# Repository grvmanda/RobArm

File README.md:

# RobArm

potential 6 DOF (maybe lower) 3D printed robotic arm. 

The repo is very rudimentary at the moment (CAD stored on Fusion 360's cloud); the code is based on ROS melodic.
The target platform is RPi4.

Custom stepper motor driver board (and boards for limit switches) designed on KiCad are also stored on this repo.

preview of rev 1 driver board:

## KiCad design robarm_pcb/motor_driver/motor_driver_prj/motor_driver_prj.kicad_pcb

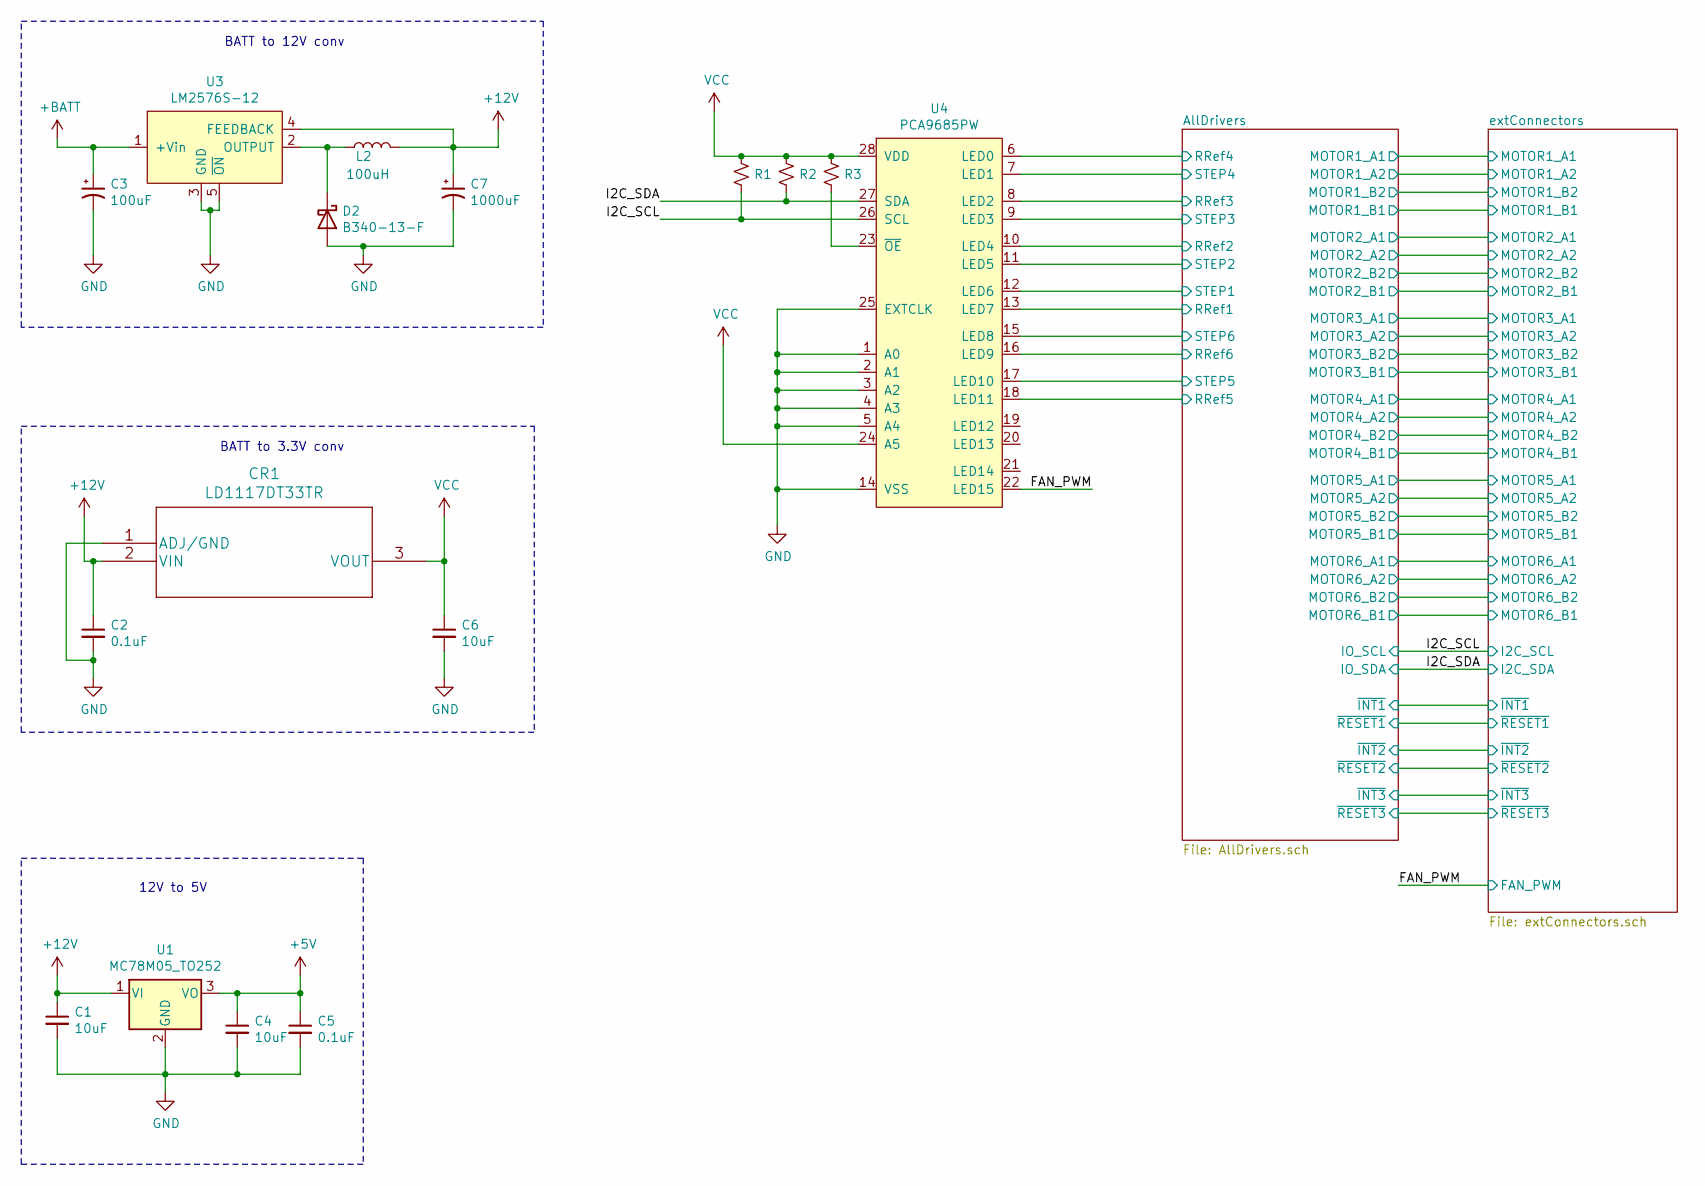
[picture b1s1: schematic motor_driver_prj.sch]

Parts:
C1, C4, C6: 10uF; C_0805_2012Metric_Pad1.18x1.45mm_HandSolder
C2, C5: 0.1uF; C_0603_1608Metric_Pad1.08x0.95mm_HandSolder
C3: 100uF; CP_Elec_8x6.2
C7: 1000uF; CP_Elec_8x6.2
CR1: LD1117DT33TR
D2: B340-13-F
L2: 100uH; SRR1280A-101M
R1, R2, R3: R_Small_US; R_0603_1608Metric_Pad0.98x0.95mm_HandSolder
U1: MC78M05_TO252; TO-252-2
U3: LM2576S-12; LM2576SX_TO263-5
U4: PCA9685PW; PC9685_TSSOP28

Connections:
+5V: C4.1, C5.1, U1.3 (VO); also elsewhere on the board
+12V: C1.1, C2.1, C7.1, CR1.2 (VIN), L2.2, U1.1 (VI), U3.4 (FEEDBACK); also elsewhere on the board
+BATT: C3.1, U3.1 (+Vin); also elsewhere on the board
/AllDrivers/RRef1: U4.13 (LED7); also elsewhere on the board
/AllDrivers/RRef2: U4.10 (LED4); also elsewhere on the board
/AllDrivers/RRef3: U4.8 (LED2); also elsewhere on the board
/AllDrivers/RRef4: U4.6 (LED0); also elsewhere on the board
/AllDrivers/RRef5: U4.18 (LED11); also elsewhere on the board
/AllDrivers/RRef6: U4.16 (LED9); also elsewhere on the board
/AllDrivers/STEP1: U4.12 (LED6); also elsewhere on the board
/AllDrivers/STEP2: U4.11 (LED5); also elsewhere on the board
/AllDrivers/STEP3: U4.9 (LED3); also elsewhere on the board
/AllDrivers/STEP4: U4.7 (LED1); also elsewhere on the board
/AllDrivers/STEP5: U4.17 (LED10); also elsewhere on the board
/AllDrivers/STEP6: U4.15 (LED8); also elsewhere on the board
/FAN_PWM: U4.22 (LED15); also elsewhere on the board
/I2C_SCL: R1.2, U4.26 (SCL); also elsewhere on the board
/I2C_SDA: R2.2, U4.27 (SDA); also elsewhere on the board
GND: C1.2, C2.2, C3.2, C4.2, C5.2, C6.2, C7.2, CR1.1 (ADJ/GND), D2.2 (A), U1.2 (GND), U3.3 (GND), U3.5 (~ON), U4.1 (A0), U4.2 (A1), U4.3 (A2), U4.4 (A3), U4.5 (A4), U4.14 (VSS), U4.25 (EXTCLK); also elsewhere on the board
unnamed: D2.1 (K), L2.1, U3.2 (OUTPUT)
unnamed: R3.2, U4.23 (~OE)
VCC: C6.1, CR1.3 (VOUT), R1.1, R2.1, R3.1, U4.24 (A5), U4.28 (VDD); also elsewhere on the board

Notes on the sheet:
BATT to 12V conv
12V to 5V
BATT to 3.3V conv

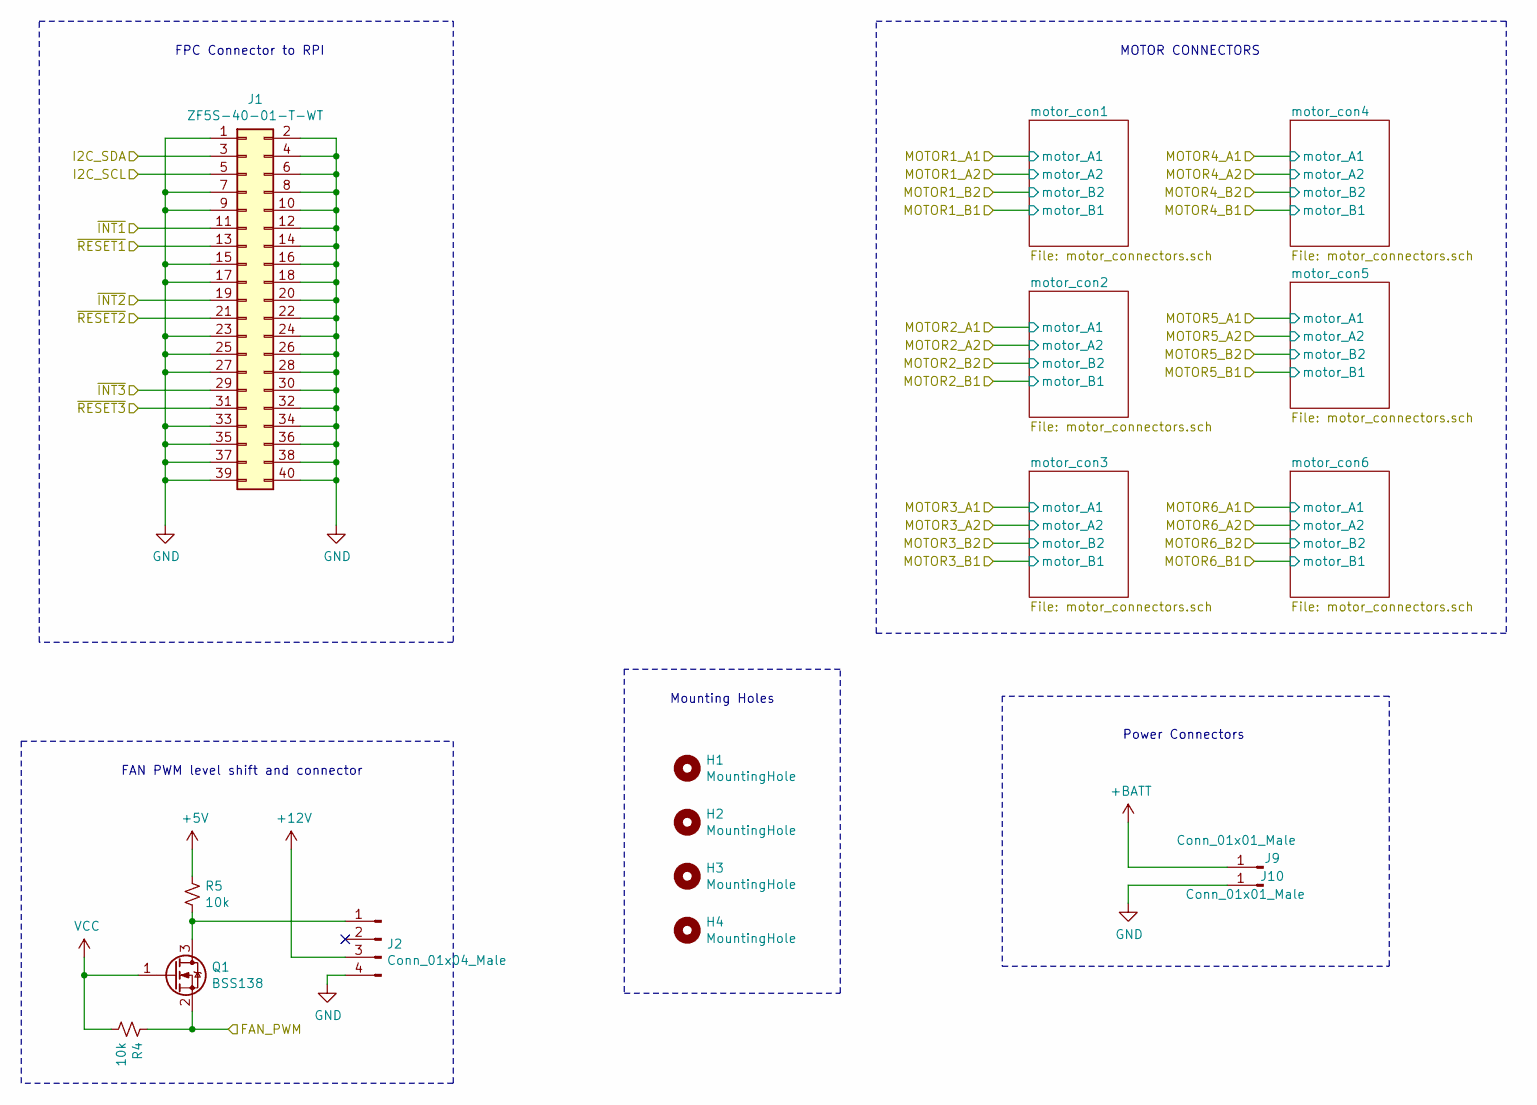
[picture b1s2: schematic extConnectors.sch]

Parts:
H1, H2, H3, H4: MountingHole; MountingHole_3.2mm_M3_ISO14580
J1: ZF5S-40-01-T-WT; FPC_40
J2: Conn_01x04_Male; FanPinHeader_1x04_P2.54mm_Vertical
J9, J10: Conn_01x01_Male; TestPoint_Pad_4.0x4.0mm
Q1: BSS138; SOT-23
R4, R5: 10k; R_0603_1608Metric_Pad0.98x0.95mm_HandSolder

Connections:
+5V: R5.1; also elsewhere on the board
+12V: J2.3; also elsewhere on the board
+BATT: J9.1; also elsewhere on the board
/AllDrivers/~INT1: J1.11; also elsewhere on the board
/AllDrivers/~INT2: J1.19; also elsewhere on the board
/AllDrivers/~INT3: J1.29; also elsewhere on the board
/AllDrivers/~RESET1: J1.13; also elsewhere on the board
/AllDrivers/~RESET2: J1.21; also elsewhere on the board
/AllDrivers/~RESET3: J1.31; also elsewhere on the board
/FAN_PWM: Q1.2 (S), R4.1; also elsewhere on the board
/I2C_SCL: J1.5; also elsewhere on the board
/I2C_SDA: J1.3; also elsewhere on the board
GND: J1.1, J1.2, J1.4, J1.6, J1.7, J1.8, J1.9, J1.10, J1.12, J1.14, J1.15, J1.16, J1.17, J1.18, J1.20, J1.22, J1.23, J1.24, J1.25, J1.26, J1.27, J1.28, J1.30, J1.32, J1.33, J1.34, J1.35, J1.36, J1.37, J1.38, J1.39, J1.40, J2.4, J10.1; also elsewhere on the board
unnamed: J2.1, Q1.3 (D), R5.2
VCC: Q1.1 (G), R4.2; also elsewhere on the board

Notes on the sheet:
MOTOR CONNECTORS
FPC Connector to RPI
FAN PWM level shift and connector
Power Connectors
Mounting Holes

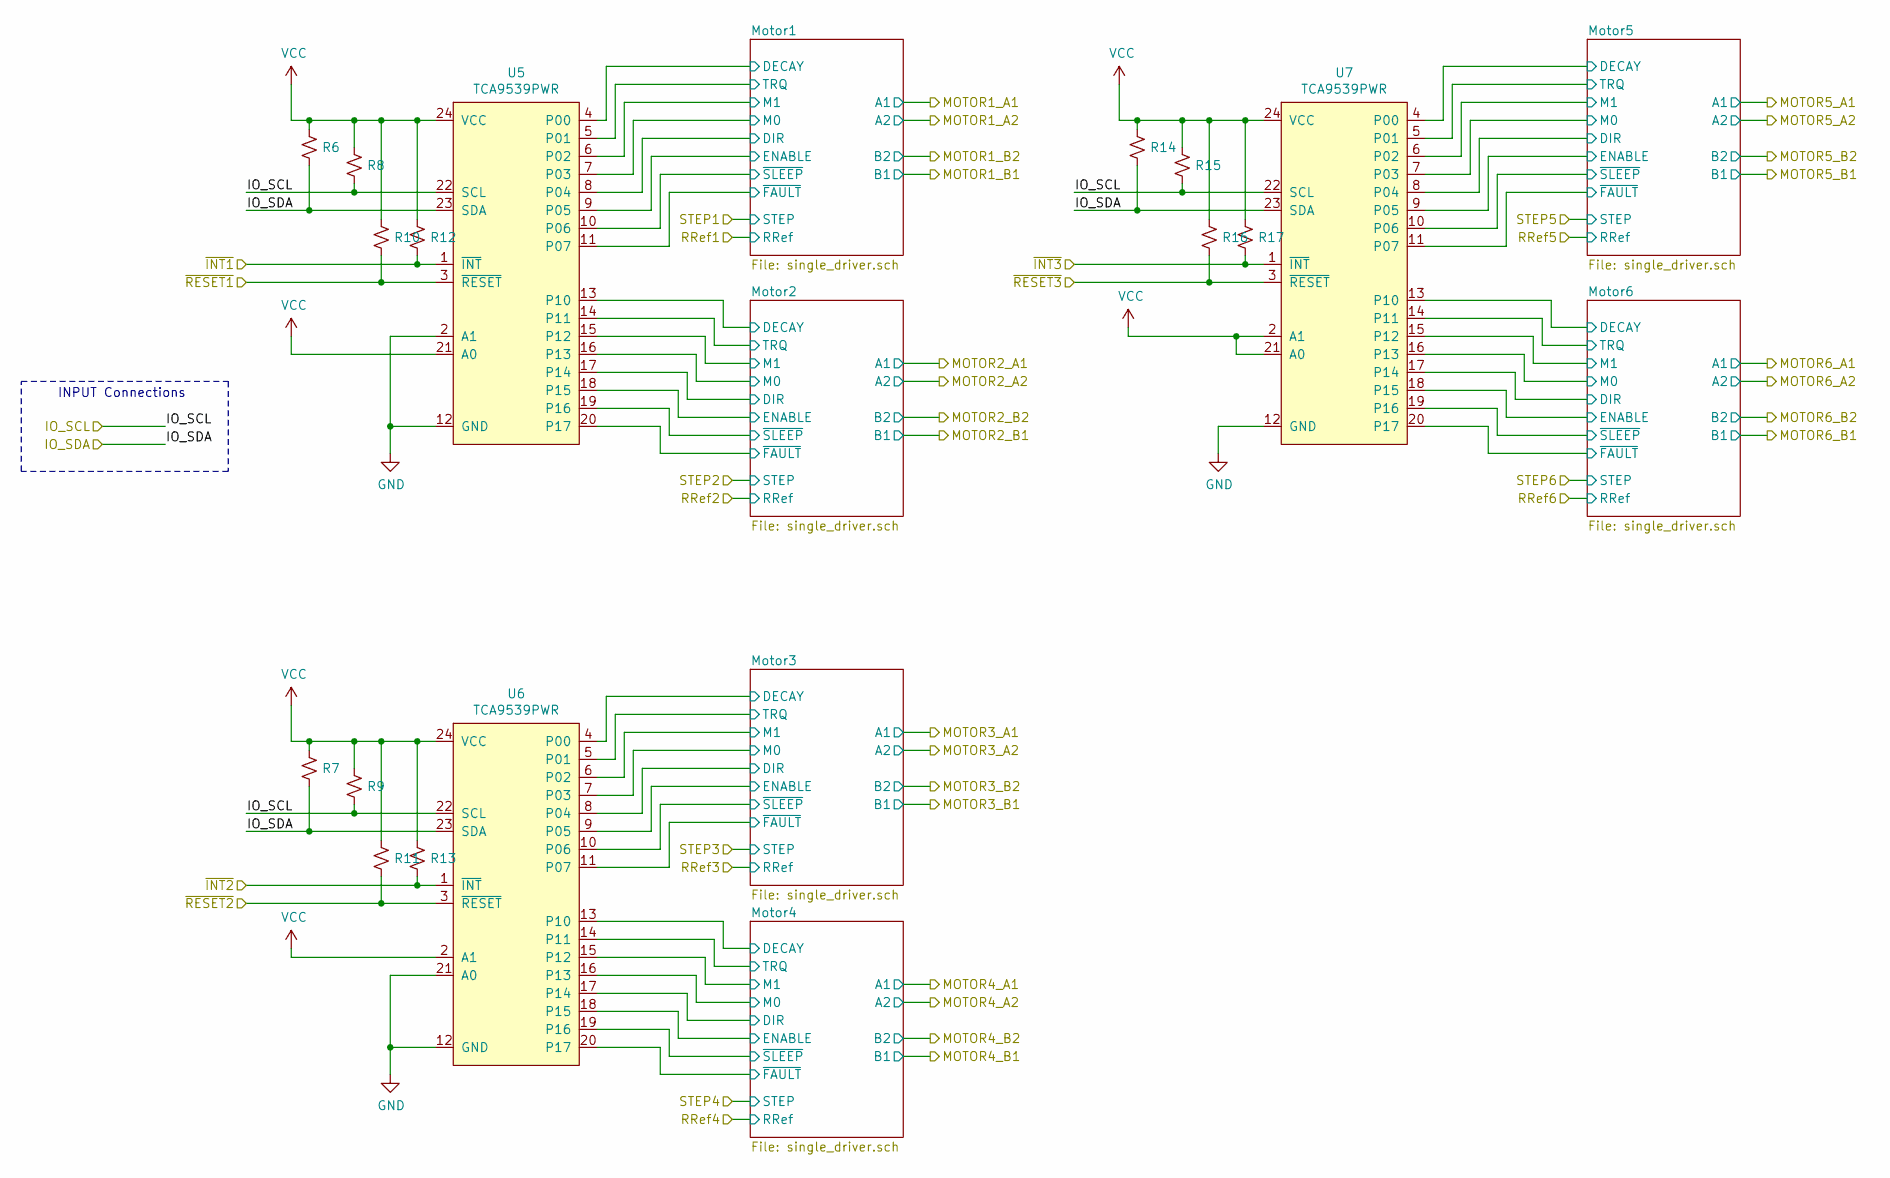
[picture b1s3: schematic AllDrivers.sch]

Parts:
R6, R7, R8, R9, R10, R11, R12, R13, R14, R15, R16, R17: 1; R_0603_1608Metric_Pad0.98x0.95mm_HandSolder
U5, U6, U7: TCA9539PWR; TCA9539_TSSOP-24

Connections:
/AllDrivers/Motor1/DECAY: U5.4 (P00); also elsewhere on the board
/AllDrivers/Motor1/DIR: U5.8 (P04); also elsewhere on the board
/AllDrivers/Motor1/ENABLE: U5.9 (P05); also elsewhere on the board
/AllDrivers/Motor1/M0: U5.7 (P03); also elsewhere on the board
/AllDrivers/Motor1/M1: U5.6 (P02); also elsewhere on the board
/AllDrivers/Motor1/TRQ: U5.5 (P01); also elsewhere on the board
/AllDrivers/Motor1/~FAULT: U5.11 (P07); also elsewhere on the board
/AllDrivers/Motor1/~SLEEP: U5.10 (P06); also elsewhere on the board
/AllDrivers/Motor2/DECAY: U5.13 (P10); also elsewhere on the board
/AllDrivers/Motor2/DIR: U5.17 (P14); also elsewhere on the board
/AllDrivers/Motor2/ENABLE: U5.18 (P15); also elsewhere on the board
/AllDrivers/Motor2/M0: U5.16 (P13); also elsewhere on the board
/AllDrivers/Motor2/M1: U5.15 (P12); also elsewhere on the board
/AllDrivers/Motor2/TRQ: U5.14 (P11); also elsewhere on the board
/AllDrivers/Motor2/~FAULT: U5.20 (P17); also elsewhere on the board
/AllDrivers/Motor2/~SLEEP: U5.19 (P16); also elsewhere on the board
/AllDrivers/Motor3/DECAY: U6.4 (P00); also elsewhere on the board
/AllDrivers/Motor3/DIR: U6.8 (P04); also elsewhere on the board
/AllDrivers/Motor3/ENABLE: U6.9 (P05); also elsewhere on the board
/AllDrivers/Motor3/M0: U6.7 (P03); also elsewhere on the board
/AllDrivers/Motor3/M1: U6.6 (P02); also elsewhere on the board
/AllDrivers/Motor3/TRQ: U6.5 (P01); also elsewhere on the board
/AllDrivers/Motor3/~FAULT: U6.11 (P07); also elsewhere on the board
/AllDrivers/Motor3/~SLEEP: U6.10 (P06); also elsewhere on the board
/AllDrivers/Motor4/DECAY: U6.13 (P10); also elsewhere on the board
/AllDrivers/Motor4/DIR: U6.17 (P14); also elsewhere on the board
/AllDrivers/Motor4/ENABLE: U6.18 (P15); also elsewhere on the board
/AllDrivers/Motor4/M0: U6.16 (P13); also elsewhere on the board
/AllDrivers/Motor4/M1: U6.15 (P12); also elsewhere on the board
/AllDrivers/Motor4/TRQ: U6.14 (P11); also elsewhere on the board
/AllDrivers/Motor4/~FAULT: U6.20 (P17); also elsewhere on the board
/AllDrivers/Motor4/~SLEEP: U6.19 (P16); also elsewhere on the board
/AllDrivers/Motor5/DECAY: U7.4 (P00); also elsewhere on the board
/AllDrivers/Motor5/DIR: U7.8 (P04); also elsewhere on the board
/AllDrivers/Motor5/ENABLE: U7.9 (P05); also elsewhere on the board
/AllDrivers/Motor5/M0: U7.7 (P03); also elsewhere on the board
/AllDrivers/Motor5/M1: U7.6 (P02); also elsewhere on the board
/AllDrivers/Motor5/TRQ: U7.5 (P01); also elsewhere on the board
/AllDrivers/Motor5/~FAULT: U7.11 (P07); also elsewhere on the board
/AllDrivers/Motor5/~SLEEP: U7.10 (P06); also elsewhere on the board
/AllDrivers/Motor6/DECAY: U7.13 (P10); also elsewhere on the board
/AllDrivers/Motor6/DIR: U7.17 (P14); also elsewhere on the board
/AllDrivers/Motor6/ENABLE: U7.18 (P15); also elsewhere on the board
/AllDrivers/Motor6/M0: U7.16 (P13); also elsewhere on the board
/AllDrivers/Motor6/M1: U7.15 (P12); also elsewhere on the board
/AllDrivers/Motor6/TRQ: U7.14 (P11); also elsewhere on the board
/AllDrivers/Motor6/~FAULT: U7.20 (P17); also elsewhere on the board
/AllDrivers/Motor6/~SLEEP: U7.19 (P16); also elsewhere on the board
/AllDrivers/~INT1: R12.2, U5.1 (~INT); also elsewhere on the board
/AllDrivers/~INT2: R13.2, U6.1 (~INT); also elsewhere on the board
/AllDrivers/~INT3: R17.2, U7.1 (~INT); also elsewhere on the board
/AllDrivers/~RESET1: R10.2, U5.3 (~RESET); also elsewhere on the board
/AllDrivers/~RESET2: R11.2, U6.3 (~RESET); also elsewhere on the board
/AllDrivers/~RESET3: R16.2, U7.3 (~RESET); also elsewhere on the board
/I2C_SCL: R8.2, R9.2, R15.2, U5.22 (SCL), U6.22 (SCL), U7.22 (SCL); also elsewhere on the board
/I2C_SDA: R6.2, R7.2, R14.2, U5.23 (SDA), U6.23 (SDA), U7.23 (SDA); also elsewhere on the board
GND: U5.2 (A1), U5.12 (GND), U6.12 (GND), U6.21 (A0), U7.12 (GND); also elsewhere on the board
VCC: R6.1, R7.1, R8.1, R9.1, R10.1, R11.1, R12.1, R13.1, R14.1, R15.1, R16.1, R17.1, U5.21 (A0), U5.24 (VCC), U6.2 (A1), U6.24 (VCC), U7.2 (A1), U7.21 (A0), U7.24 (VCC); also elsewhere on the board

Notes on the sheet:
INPUT Connections

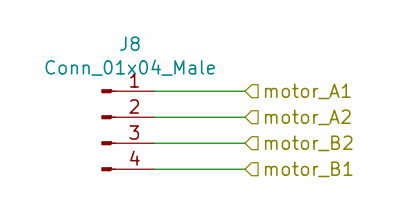
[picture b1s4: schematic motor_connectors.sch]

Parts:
J3: Conn_01x04_Male; PhoenixContact_MSTBVA_2,5_4-G-5,08_1x04_P5.08mm_Vertical

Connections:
/AllDrivers/MOTOR1_A1: J3.1; also elsewhere on the board
/AllDrivers/MOTOR1_A2: J3.2; also elsewhere on the board
/AllDrivers/MOTOR1_B1: J3.4; also elsewhere on the board
/AllDrivers/MOTOR1_B2: J3.3; also elsewhere on the board

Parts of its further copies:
J4, J5, J6, J7, J8: Conn_01x04_Male; PhoenixContact_MSTBVA_2,5_4-G-5,08_1x04_P5.08mm_Vertical

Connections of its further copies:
/AllDrivers/MOTOR2_A1: J4.1; also elsewhere on the board
/AllDrivers/MOTOR2_A2: J4.2; also elsewhere on the board
/AllDrivers/MOTOR2_B1: J4.4; also elsewhere on the board
/AllDrivers/MOTOR2_B2: J4.3; also elsewhere on the board
/AllDrivers/MOTOR3_A1: J5.1; also elsewhere on the board
/AllDrivers/MOTOR3_A2: J5.2; also elsewhere on the board
/AllDrivers/MOTOR3_B1: J5.4; also elsewhere on the board
/AllDrivers/MOTOR3_B2: J5.3; also elsewhere on the board
/AllDrivers/MOTOR4_A1: J6.1; also elsewhere on the board
/AllDrivers/MOTOR4_A2: J6.2; also elsewhere on the board
/AllDrivers/MOTOR4_B1: J6.4; also elsewhere on the board
/AllDrivers/MOTOR4_B2: J6.3; also elsewhere on the board
/AllDrivers/MOTOR5_A1: J7.1; also elsewhere on the board
/AllDrivers/MOTOR5_A2: J7.2; also elsewhere on the board
/AllDrivers/MOTOR5_B1: J7.4; also elsewhere on the board
/AllDrivers/MOTOR5_B2: J7.3; also elsewhere on the board
/AllDrivers/MOTOR6_A1: J8.1; also elsewhere on the board
/AllDrivers/MOTOR6_A2: J8.2; also elsewhere on the board
/AllDrivers/MOTOR6_B1: J8.4; also elsewhere on the board
/AllDrivers/MOTOR6_B2: J8.3; also elsewhere on the board

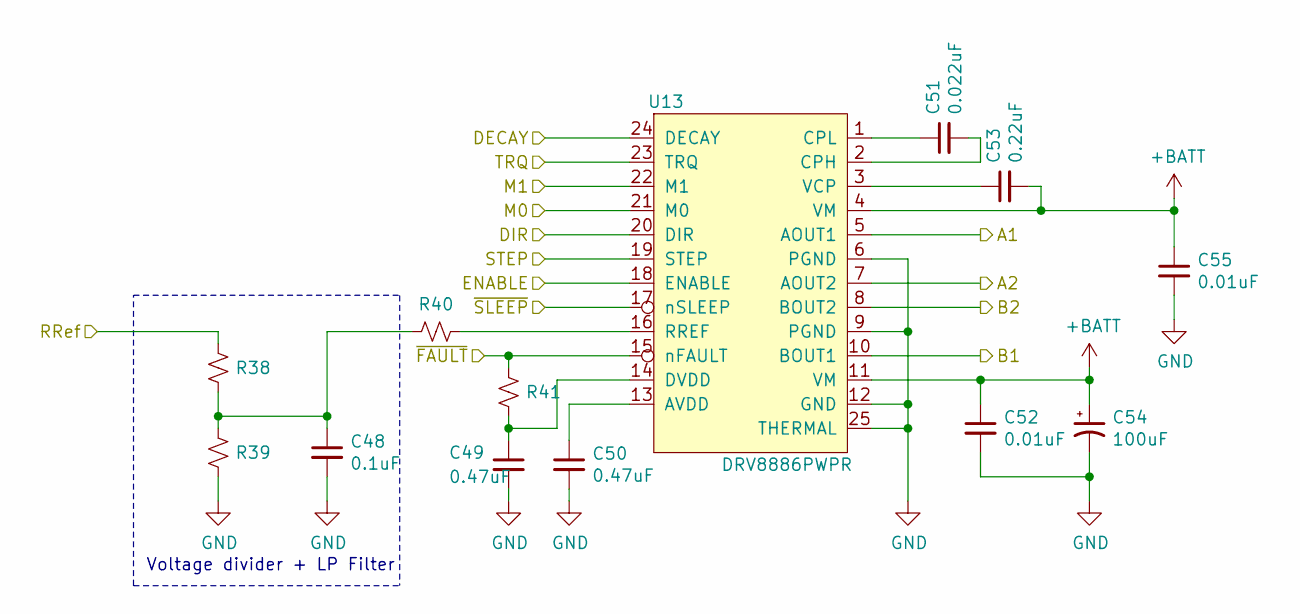
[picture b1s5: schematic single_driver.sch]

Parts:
C8: 0.1uF; C_0603_1608Metric_Pad1.08x0.95mm_HandSolder
C9, C10: 0.47uF; C_0805_2012Metric_Pad1.18x1.45mm_HandSolder
C11: 0.022uF; C_0603_1608Metric_Pad1.08x0.95mm_HandSolder
C12, C15: 0.01uF; C_0603_1608Metric_Pad1.08x0.95mm_HandSolder
C13: 0.22uF; C_0603_1608Metric_Pad1.08x0.95mm_HandSolder
C14: 100uF; CP_Elec_8x6.2
R18, R19, R21: R_Small_US; R_0603_1608Metric_Pad0.98x0.95mm_HandSolder
R20: rref; R_0603_1608Metric_Pad0.98x0.95mm_HandSolder
U8: DRV8886PWPR‎; DRV8886_HTSSOP-24

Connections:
+BATT: C12.1, C13.2, C14.1, C15.1, U8.4 (VM), U8.11 (VM); also elsewhere on the board
/AllDrivers/MOTOR4_A1: U8.5 (AOUT1); also elsewhere on the board
/AllDrivers/MOTOR4_A2: U8.7 (AOUT2); also elsewhere on the board
/AllDrivers/MOTOR4_B1: U8.10 (BOUT1); also elsewhere on the board
/AllDrivers/MOTOR4_B2: U8.8 (BOUT2); also elsewhere on the board
/AllDrivers/Motor4/DECAY: U8.24 (DECAY); also elsewhere on the board
/AllDrivers/Motor4/DIR: U8.20 (DIR); also elsewhere on the board
/AllDrivers/Motor4/ENABLE: U8.18 (ENABLE); also elsewhere on the board
/AllDrivers/Motor4/M0: U8.21 (M0); also elsewhere on the board
/AllDrivers/Motor4/M1: U8.22 (M1); also elsewhere on the board
/AllDrivers/Motor4/TRQ: U8.23 (TRQ); also elsewhere on the board
/AllDrivers/Motor4/~FAULT: R21.1, U8.15 (nFAULT); also elsewhere on the board
/AllDrivers/Motor4/~SLEEP: U8.17 (nSLEEP); also elsewhere on the board
/AllDrivers/RRef4: R18.1; also elsewhere on the board
/AllDrivers/STEP4: U8.19 (STEP); also elsewhere on the board
GND: C8.2, C9.2, C10.2, C12.2, C14.2, C15.2, R19.2, U8.6 (PGND), U8.9 (PGND), U8.12 (GND), U8.25 (THERMAL); also elsewhere on the board
unnamed: C8.1, R18.2, R19.1, R20.1
unnamed: C9.1, R21.2, U8.14 (DVDD)
unnamed: C10.1, U8.13 (AVDD)
unnamed: C11.1, U8.1 (CPL)
unnamed: C11.2, U8.2 (CPH)
unnamed: C13.1, U8.3 (VCP)
unnamed: R20.2, U8.16 (RREF)

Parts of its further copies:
C16, C24, C32, C40, C48: 0.1uF; C_0603_1608Metric_Pad1.08x0.95mm_HandSolder
C17, C18, C25, C26, C33, C34, C41, C42, C49, C50: 0.47uF; C_0805_2012Metric_Pad1.18x1.45mm_HandSolder
C19, C27, C35, C43, C51: 0.022uF; C_0603_1608Metric_Pad1.08x0.95mm_HandSolder
C20, C23, C28, C31, C36, C39, C44, C47, C52, C55: 0.01uF; C_0603_1608Metric_Pad1.08x0.95mm_HandSolder
C21, C29, C37, C45, C53: 0.22uF; C_0603_1608Metric_Pad1.08x0.95mm_HandSolder
C22, C30, C38, C46, C54: 100uF; CP_Elec_8x6.2
R22, R23, R25, R26, R27, R29, R30, R31, R33, R34, R35, R37, R38, R39, R41: R_Small_US; R_0603_1608Metric_Pad0.98x0.95mm_HandSolder
R24, R28, R32, R36, R40: rref; R_0603_1608Metric_Pad0.98x0.95mm_HandSolder
U9, U10, U11, U12, U13: DRV8886PWPR‎; DRV8886_HTSSOP-24

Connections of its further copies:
+BATT: C20.1, C21.2, C22.1, C23.1, C28.1, C29.2, C30.1, C31.1, C36.1, C37.2, C38.1, C39.1, C44.1, C45.2, C46.1, C47.1, C52.1, C53.2, C54.1, C55.1, U9.4 (VM), U9.11 (VM), U10.4 (VM), U10.11 (VM), U11.4 (VM), U11.11 (VM), U12.4 (VM), U12.11 (VM), U13.4 (VM), U13.11 (VM); also elsewhere on the board
/AllDrivers/MOTOR1_A1: U11.5 (AOUT1); also elsewhere on the board
/AllDrivers/MOTOR1_A2: U11.7 (AOUT2); also elsewhere on the board
/AllDrivers/MOTOR1_B1: U11.10 (BOUT1); also elsewhere on the board
/AllDrivers/MOTOR1_B2: U11.8 (BOUT2); also elsewhere on the board
/AllDrivers/MOTOR2_A1: U10.5 (AOUT1); also elsewhere on the board
/AllDrivers/MOTOR2_A2: U10.7 (AOUT2); also elsewhere on the board
/AllDrivers/MOTOR2_B1: U10.10 (BOUT1); also elsewhere on the board
/AllDrivers/MOTOR2_B2: U10.8 (BOUT2); also elsewhere on the board
/AllDrivers/MOTOR3_A1: U9.5 (AOUT1); also elsewhere on the board
/AllDrivers/MOTOR3_A2: U9.7 (AOUT2); also elsewhere on the board
/AllDrivers/MOTOR3_B1: U9.10 (BOUT1); also elsewhere on the board
/AllDrivers/MOTOR3_B2: U9.8 (BOUT2); also elsewhere on the board
/AllDrivers/MOTOR5_A1: U12.5 (AOUT1); also elsewhere on the board
/AllDrivers/MOTOR5_A2: U12.7 (AOUT2); also elsewhere on the board
/AllDrivers/MOTOR5_B1: U12.10 (BOUT1); also elsewhere on the board
/AllDrivers/MOTOR5_B2: U12.8 (BOUT2); also elsewhere on the board
/AllDrivers/MOTOR6_A1: U13.5 (AOUT1); also elsewhere on the board
/AllDrivers/MOTOR6_A2: U13.7 (AOUT2); also elsewhere on the board
/AllDrivers/MOTOR6_B1: U13.10 (BOUT1); also elsewhere on the board
/AllDrivers/MOTOR6_B2: U13.8 (BOUT2); also elsewhere on the board
/AllDrivers/Motor1/DECAY: U11.24 (DECAY); also elsewhere on the board
/AllDrivers/Motor1/DIR: U11.20 (DIR); also elsewhere on the board
/AllDrivers/Motor1/ENABLE: U11.18 (ENABLE); also elsewhere on the board
/AllDrivers/Motor1/M0: U11.21 (M0); also elsewhere on the board
/AllDrivers/Motor1/M1: U11.22 (M1); also elsewhere on the board
/AllDrivers/Motor1/TRQ: U11.23 (TRQ); also elsewhere on the board
/AllDrivers/Motor1/~FAULT: R33.1, U11.15 (nFAULT); also elsewhere on the board
/AllDrivers/Motor1/~SLEEP: U11.17 (nSLEEP); also elsewhere on the board
/AllDrivers/Motor2/DECAY: U10.24 (DECAY); also elsewhere on the board
/AllDrivers/Motor2/DIR: U10.20 (DIR); also elsewhere on the board
/AllDrivers/Motor2/ENABLE: U10.18 (ENABLE); also elsewhere on the board
/AllDrivers/Motor2/M0: U10.21 (M0); also elsewhere on the board
/AllDrivers/Motor2/M1: U10.22 (M1); also elsewhere on the board
/AllDrivers/Motor2/TRQ: U10.23 (TRQ); also elsewhere on the board
/AllDrivers/Motor2/~FAULT: R29.1, U10.15 (nFAULT); also elsewhere on the board
/AllDrivers/Motor2/~SLEEP: U10.17 (nSLEEP); also elsewhere on the board
/AllDrivers/Motor3/DECAY: U9.24 (DECAY); also elsewhere on the board
/AllDrivers/Motor3/DIR: U9.20 (DIR); also elsewhere on the board
/AllDrivers/Motor3/ENABLE: U9.18 (ENABLE); also elsewhere on the board
/AllDrivers/Motor3/M0: U9.21 (M0); also elsewhere on the board
/AllDrivers/Motor3/M1: U9.22 (M1); also elsewhere on the board
/AllDrivers/Motor3/TRQ: U9.23 (TRQ); also elsewhere on the board
/AllDrivers/Motor3/~FAULT: R25.1, U9.15 (nFAULT); also elsewhere on the board
/AllDrivers/Motor3/~SLEEP: U9.17 (nSLEEP); also elsewhere on the board
/AllDrivers/Motor5/DECAY: U12.24 (DECAY); also elsewhere on the board
/AllDrivers/Motor5/DIR: U12.20 (DIR); also elsewhere on the board
/AllDrivers/Motor5/ENABLE: U12.18 (ENABLE); also elsewhere on the board
/AllDrivers/Motor5/M0: U12.21 (M0); also elsewhere on the board
/AllDrivers/Motor5/M1: U12.22 (M1); also elsewhere on the board
/AllDrivers/Motor5/TRQ: U12.23 (TRQ); also elsewhere on the board
/AllDrivers/Motor5/~FAULT: R37.1, U12.15 (nFAULT); also elsewhere on the board
/AllDrivers/Motor5/~SLEEP: U12.17 (nSLEEP); also elsewhere on the board
/AllDrivers/Motor6/DECAY: U13.24 (DECAY); also elsewhere on the board
/AllDrivers/Motor6/DIR: U13.20 (DIR); also elsewhere on the board
/AllDrivers/Motor6/ENABLE: U13.18 (ENABLE); also elsewhere on the board
/AllDrivers/Motor6/M0: U13.21 (M0); also elsewhere on the board
/AllDrivers/Motor6/M1: U13.22 (M1); also elsewhere on the board
/AllDrivers/Motor6/TRQ: U13.23 (TRQ); also elsewhere on the board
/AllDrivers/Motor6/~FAULT: R41.1, U13.15 (nFAULT); also elsewhere on the board
/AllDrivers/Motor6/~SLEEP: U13.17 (nSLEEP); also elsewhere on the board
/AllDrivers/RRef1: R30.1; also elsewhere on the board
/AllDrivers/RRef2: R26.1; also elsewhere on the board
/AllDrivers/RRef3: R22.1; also elsewhere on the board
/AllDrivers/RRef5: R34.1; also elsewhere on the board
/AllDrivers/RRef6: R38.1; also elsewhere on the board
/AllDrivers/STEP1: U11.19 (STEP); also elsewhere on the board
/AllDrivers/STEP2: U10.19 (STEP); also elsewhere on the board
/AllDrivers/STEP3: U9.19 (STEP); also elsewhere on the board
/AllDrivers/STEP5: U12.19 (STEP); also elsewhere on the board
/AllDrivers/STEP6: U13.19 (STEP); also elsewhere on the board
GND: C16.2, C17.2, C18.2, C20.2, C22.2, C23.2, C24.2, C25.2, C26.2, C28.2, C30.2, C31.2, C32.2, C33.2, C34.2, C36.2, C38.2, C39.2, C40.2, C41.2, C42.2, C44.2, C46.2, C47.2, C48.2, C49.2, C50.2, C52.2, C54.2, C55.2, R23.2, R27.2, R31.2, R35.2, R39.2, U9.6 (PGND), U9.9 (PGND), U9.12 (GND), U9.25 (THERMAL), U10.6 (PGND), U10.9 (PGND), U10.12 (GND), U10.25 (THERMAL), U11.6 (PGND), U11.9 (PGND), U11.12 (GND), U11.25 (THERMAL), U12.6 (PGND), U12.9 (PGND), U12.12 (GND), U12.25 (THERMAL), U13.6 (PGND), U13.9 (PGND), U13.12 (GND), U13.25 (THERMAL); also elsewhere on the board
unnamed: C16.1, R22.2, R23.1, R24.1
unnamed: C17.1, R25.2, U9.14 (DVDD)
unnamed: C18.1, U9.13 (AVDD)
unnamed: C19.1, U9.1 (CPL)
unnamed: C19.2, U9.2 (CPH)
unnamed: C21.1, U9.3 (VCP)
unnamed: C24.1, R26.2, R27.1, R28.1
unnamed: C25.1, R29.2, U10.14 (DVDD)
unnamed: C26.1, U10.13 (AVDD)
unnamed: C27.1, U10.1 (CPL)
unnamed: C27.2, U10.2 (CPH)
unnamed: C29.1, U10.3 (VCP)
unnamed: C32.1, R30.2, R31.1, R32.1
unnamed: C33.1, R33.2, U11.14 (DVDD)
unnamed: C34.1, U11.13 (AVDD)
unnamed: C35.1, U11.1 (CPL)
unnamed: C35.2, U11.2 (CPH)
unnamed: C37.1, U11.3 (VCP)
unnamed: C40.1, R34.2, R35.1, R36.1
unnamed: C41.1, R37.2, U12.14 (DVDD)
unnamed: C42.1, U12.13 (AVDD)
unnamed: C43.1, U12.1 (CPL)
unnamed: C43.2, U12.2 (CPH)
unnamed: C45.1, U12.3 (VCP)
unnamed: C48.1, R38.2, R39.1, R40.1
unnamed: C49.1, R41.2, U13.14 (DVDD)
unnamed: C50.1, U13.13 (AVDD)
unnamed: C51.1, U13.1 (CPL)
unnamed: C51.2, U13.2 (CPH)
unnamed: C53.1, U13.3 (VCP)
unnamed: R24.2, U9.16 (RREF)
unnamed: R28.2, U10.16 (RREF)
unnamed: R32.2, U11.16 (RREF)
unnamed: R36.2, U12.16 (RREF)
unnamed: R40.2, U13.16 (RREF)

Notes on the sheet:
Voltage divider + LP Filter

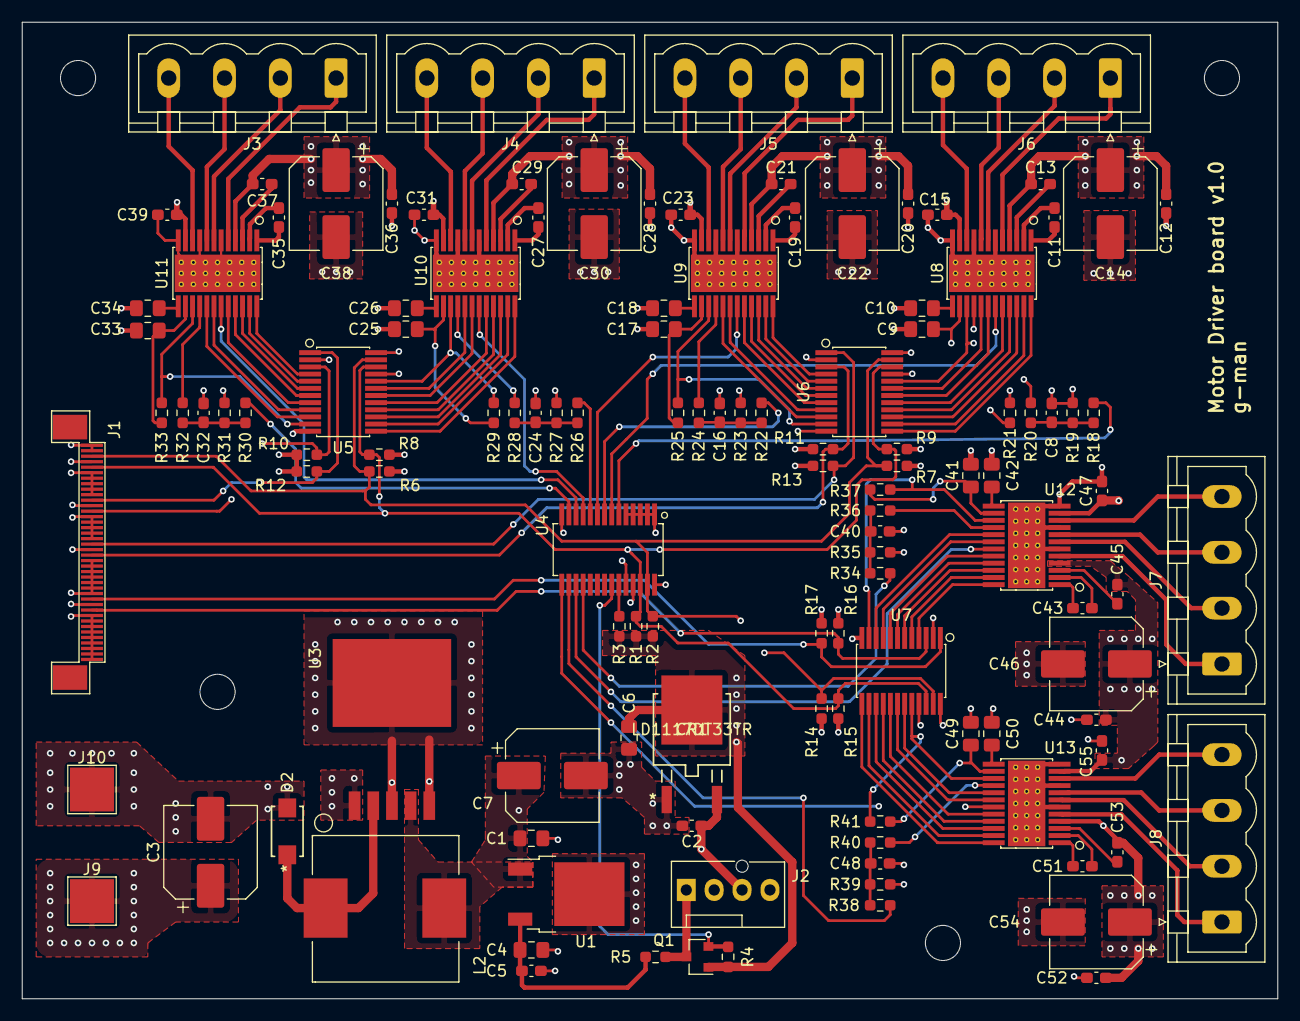
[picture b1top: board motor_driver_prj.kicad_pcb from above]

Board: 4 copper layers, 114.3 x 88.9 mm, 126 parts (0 on the bottom side), 143 nets.

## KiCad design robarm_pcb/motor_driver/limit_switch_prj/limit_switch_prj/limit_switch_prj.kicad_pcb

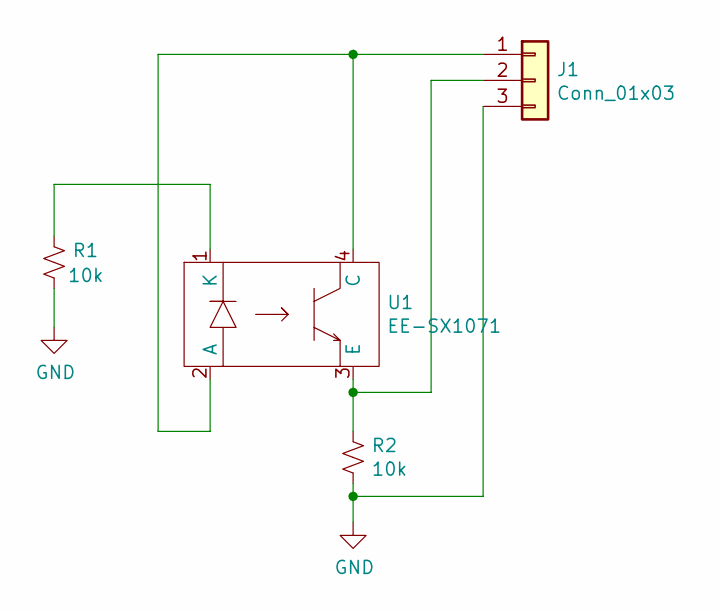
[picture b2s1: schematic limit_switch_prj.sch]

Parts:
J1: Conn_01x03; picoblade-conn-1.25mm-3pin
R1, R2: 10k; R_0603_1608Metric_Pad0.98x0.95mm_HandSolder
U1: EE-SX1071

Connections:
GND: J1.3, R1.2, R2.2
unnamed: J1.1, U1.2 (A), U1.4 (C)
unnamed: J1.2, R2.1, U1.3 (E)
unnamed: R1.1, U1.1 (K)

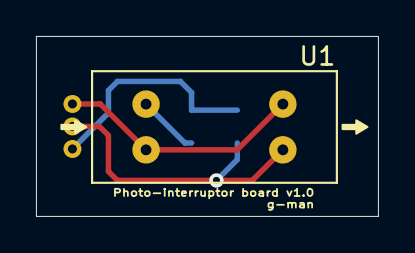
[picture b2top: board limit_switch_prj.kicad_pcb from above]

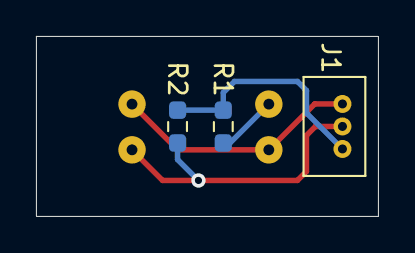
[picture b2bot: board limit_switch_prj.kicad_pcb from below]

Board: 2 copper layers, 19.0 x 10.0 mm, 4 parts (3 on the bottom side), 4 nets.

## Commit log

2020-12-26 init commit for robarm_desc package
2020-12-30 initial setup for 3 DOF arm simulations. I need to rename the files. Current plan is to do a 3 DOF arm so i can get the hang of ros-gazebo sims and then move to 6 DOF
2021-01-01 update to 3 DOF urdf - still very rudimentary. however, i will use this for testing some basic ROS code for now.
2021-01-14 spur_gear added
2021-01-14 adding stl
2021-02-09 Add motor driver PCB init
2021-02-21 update PCB schematic
2021-02-21 schematic complete?
2021-03-25 save
2021-03-28 new part placements.
2021-04-15 restructuring code
2021-04-25 Motor Driver PCB rev 1
    Motor Driver PCB rev 1
2021-04-25 gerber files for motor driver board v1.0
2021-04-25 added pictures for motor driver board
2021-05-12 working 3 joint arm
2021-05-13 add rqt test perspective
2021-05-17 update part list
2021-09-21 add DRV8711 code - initial commit
2021-10-02 add code for SPI driver portion. Also, tested that it works fine

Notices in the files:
parts and their libraries:
Copyright 2016 Accelerated Designs. All rights reserved.
